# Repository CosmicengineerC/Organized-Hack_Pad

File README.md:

# Organized-Hack_Pad
Hack pad files needed for my Hack-club Project
My hack pad has: 1 ec11 rotary encoder, 5 Mx switches, and 2 Sk6812 Mini Leds

BOM:[BOM+PRICES.pdf](https://github.com/user-attachments/files/24742580/BOM%2BPRICES.pdf)

PHOTOS:

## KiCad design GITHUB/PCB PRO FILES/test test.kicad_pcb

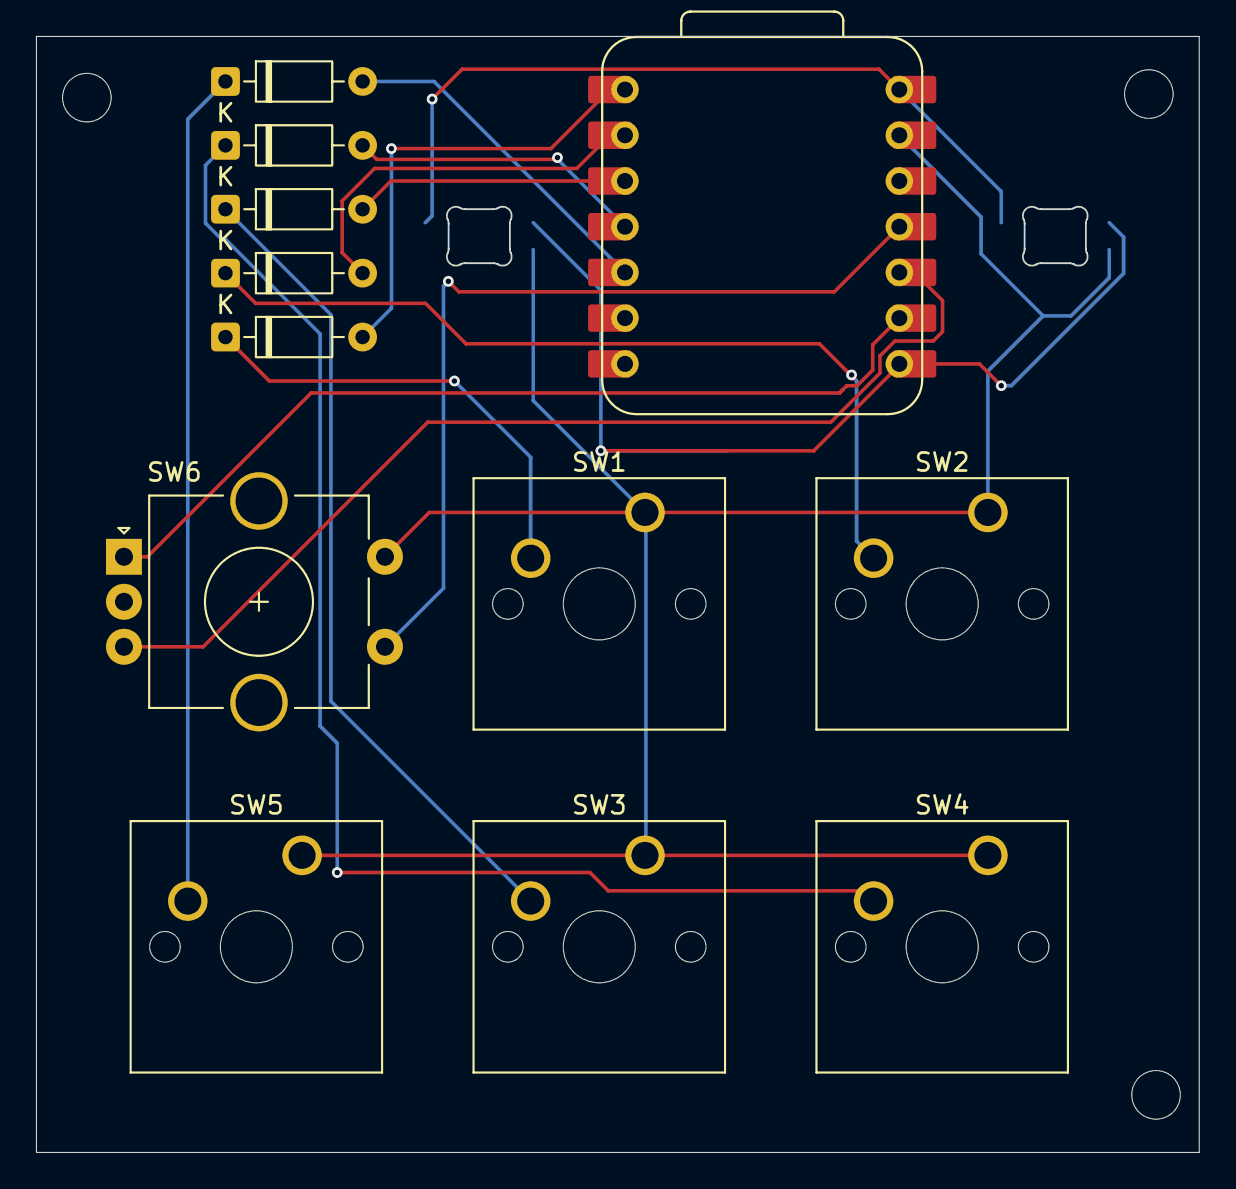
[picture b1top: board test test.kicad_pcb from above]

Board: 2 copper layers, 64.6 x 62.0 mm, 17 parts (0 on the bottom side), 16 nets.

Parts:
D1, D2: SK6812MINI-E; SK6812MINI-E_fixed
D3, D4, D5, D6, D7: 1N4148; D_DO-35_SOD27_P7.62mm_Horizontal
H1, H2, H3: MountingHole_2.7mm_M2.5
SW1, SW2, SW3, SW4, SW5: SW_Push; SW_Cherry_MX_1.00u_PCB
SW6: EC11; RotaryEncoder_Alps_EC11E-Switch_Vertical_H20mm_CircularMoun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
U1: XIAO-RP2040-DIP

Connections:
+5V: D1.1 (VDD), D2.1 (VDD), U1.14 (VBUS)
GND: D1.3 (VSS), D2.3 (VSS), SW1.1, SW2.1, SW3.1, SW4.1, SW5.1, SW6.S2, U1.13 (GND)
unnamed: D1.4 (DIN), D2.4 (DIN), U1.8 (GPIO1/RX)
unnamed: D3.2 (A), U1.5 (GPIO6/SDA)
unnamed: D3.1 (K), SW5.2
unnamed: D4.2 (A), U1.4 (GPIO29/ADC3/A3)
unnamed: D4.1 (K), SW4.2
unnamed: D5.2 (A), U1.3 (GPIO28/ADC2/A2)
unnamed: D5.1 (K), SW3.2
unnamed: D6.2 (A), U1.2 (GPIO27/ADC1/A1)
unnamed: D6.1 (K), SW2.2
unnamed: D7.2 (A), U1.1 (GPIO26/ADC0/A0)
unnamed: D7.1 (K), SW1.2
unnamed: SW6.A, U1.9 (GPIO2/SCK)
unnamed: SW6.S1, U1.11 (GPIO3/MOSI)
unnamed: SW6.B, U1.10 (GPIO4/MISO)

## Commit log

2026-01-20 Update README with components and photos
    Added details about components and images of the hack pad.
2026-01-20 Uploaded files
    All files needed to recreate my Hack-Pad
2026-01-20 Add initial implementation for rotary encoder and LEDs
    The code to upload to Xaio RP2040
2026-01-21 Add files via upload
    All updated files needed
2026-01-22 Add additional image to README photos section
